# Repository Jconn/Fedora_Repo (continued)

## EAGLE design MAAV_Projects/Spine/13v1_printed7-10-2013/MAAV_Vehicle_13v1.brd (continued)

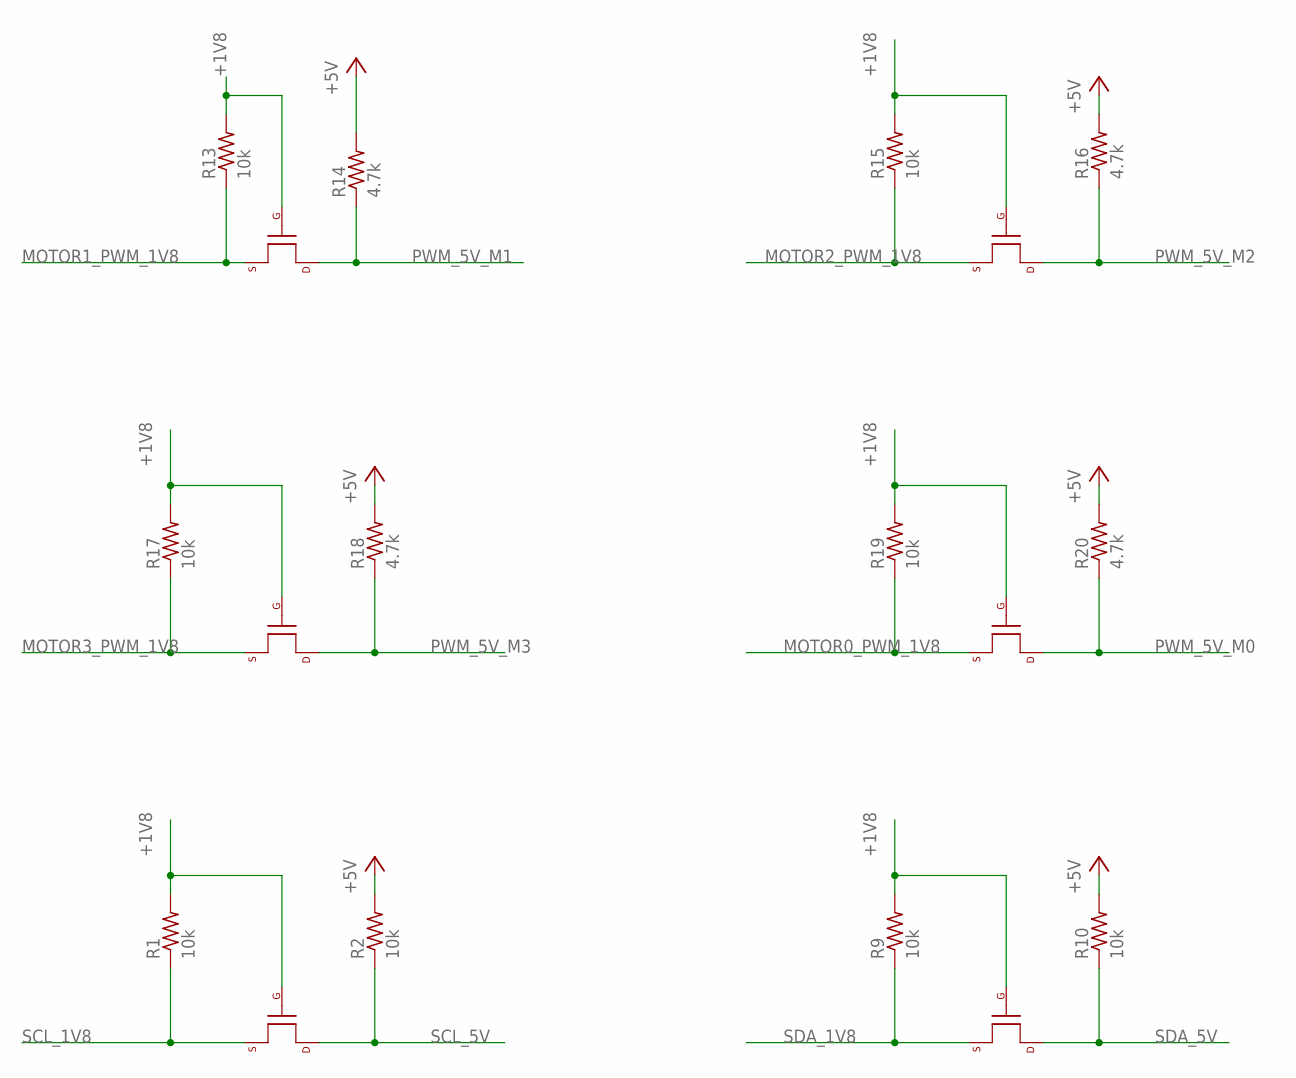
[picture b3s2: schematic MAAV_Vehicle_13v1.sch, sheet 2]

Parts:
R1, R2, R9, R10, R13, R15, R17, R19: 10k; R0603; DIGIKEY# P10.0KHCT-ND
R14, R16, R18, R20: 4.7k; R0603; DIGIKEY# P4.70KHCT-ND
T3, T4, T7, T8, T9, T10: MOSFET-NCHANNELSMD; SOT23-3; DIGIKEY# BSS138KCT-ND

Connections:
+1V8: R1.2, R9.2, R13.2, R15.2, R17.2, R19.2, T3.1 (G), T4.1 (G), T7.1 (G), T8.1 (G), T9.1 (G), T10.1 (G); also elsewhere on the board
+5V: R2.2, R10.2, R14.2, R16.2, R18.2, R20.2; also elsewhere on the board
MOTOR0_PWM_1V8: R19.1, T10.2 (S); also elsewhere on the board
MOTOR1_PWM_1V8: R13.1, T7.2 (S); also elsewhere on the board
MOTOR2_PWM_1V8: R15.1, T8.2 (S); also elsewhere on the board
MOTOR3_PWM_1V8: R17.1, T9.2 (S); also elsewhere on the board
PWM_5V_M0: R20.1, T10.3 (D); also elsewhere on the board
PWM_5V_M1: R14.1, T7.3 (D); also elsewhere on the board
PWM_5V_M2: R16.1, T8.3 (D); also elsewhere on the board
PWM_5V_M3: R18.1, T9.3 (D); also elsewhere on the board
SCL_1V8: R1.1, T3.2 (S); also elsewhere on the board
SCL_5V: R2.1, T3.3 (D); also elsewhere on the board
SDA_1V8: R9.1, T4.2 (S); also elsewhere on the board
SDA_5V: R10.1, T4.3 (D); also elsewhere on the board

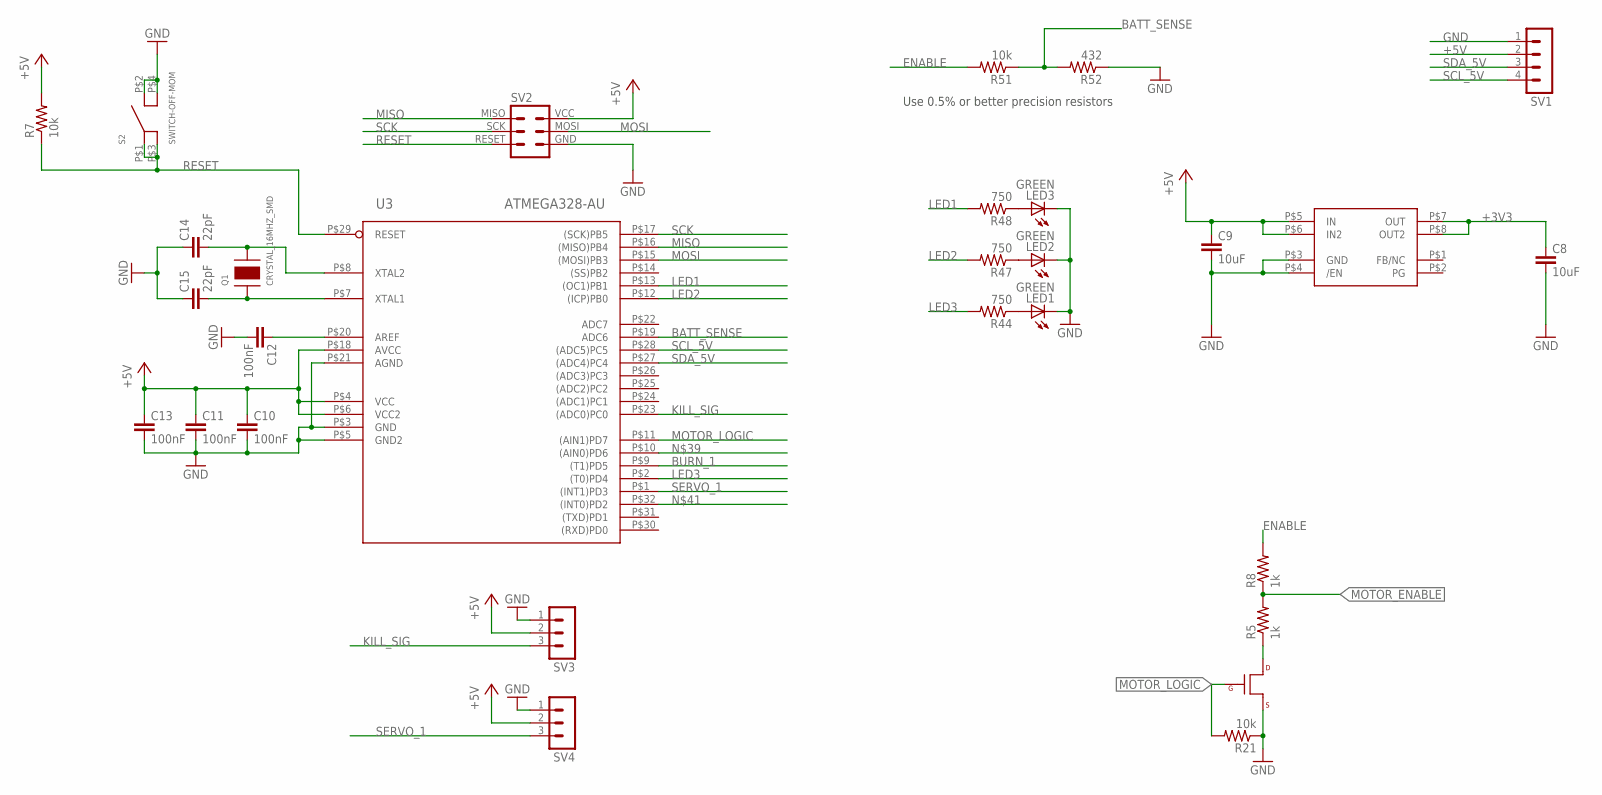
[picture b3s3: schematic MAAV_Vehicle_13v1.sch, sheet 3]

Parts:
C8, C9: 10uF; C1206; DIGIKEY# 587-2399-1-ND
C10, C11, C12, C13: 100nF; C0603; DIGIKEY# 1276-1000-1-ND
C14, C15: 22pF; C0603; DIGIKEY# 478-6200-1-ND
LED1, LED2, LED3: GREEN; CHIPLED_0603; DIGIKEY# 1080-1405-1-ND
Q1: CRYSTAL_16MHZ_SMD; 4-SMD_DFN
R5, R8: 1k; R0603; DIGIKEY# P1.00KHCT-ND
R7, R21: 10k; R0603; DIGIKEY# P10.0KHCT-ND
R44, R47, R48: 750; R0805; DIGIKEY# P750CCT-ND
R51: 10k; R0603; DIGIKEY# P10KDBCT-ND
R52: 432; R0603; DIGIKEY# P432DBCT-ND
S2: SWITCH-OFF-MOM; DIGIKEY# P11084SCT-ND
SV1: MA04-1
SV2: AVRISP-63X2_SMD; AVRISP-6-SMD
SV3, SV4: MA03-1; DIGIKEY# 3M9477-ND
T11: MOSFET-NCHANNELSMD; SOT23-3; DIGIKEY# BSS138KCT-ND
U3: ATMEGA328-AU; 32-TQFP; DIGIKEY# ATMEGA328-AU-ND
U4: REG_3V_8SOIC; 8-SOIC; DIGIKEY# 296-2719-5-ND

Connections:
+3V3: C8.1, U4.P$7 (OUT), U4.P$8 (OUT2)
+5V: C9.1, C10.1, C11.1, C13.1, R7.2, SV1.2, SV2.VCC, SV3.2, SV4.2, U3.P$4 (VCC), U3.P$6 (VCC2), U3.P$18 (AVCC), U4.P$5 (IN), U4.P$6 (IN2); also elsewhere on the board
BATT_SENSE: R51.1, R52.2, U3.P$19 (ADC6)
BURN_1: U3.P$9 ((T1)PD5); also elsewhere on the board
ENABLE: R8.2, R51.2; also elsewhere on the board
GND: C8.2, C9.2, C10.2, C11.2, C12.2, C13.2, C14.1, C15.1, LED1.C, LED2.C, LED3.C, R21.1, R52.1, S2.P$2 (P2), S2.P$4 (P4), SV1.1, SV2.GND, SV3.1, SV4.1, T11.2 (S), U3.P$3 (GND), U3.P$5 (GND2), U3.P$21 (AGND), U4.P$3 (GND), U4.P$4 (/EN); also elsewhere on the board
KILL_SIG: SV3.3, U3.P$23 ((ADC0)PC0)
LED1: R48.2, U3.P$13 ((OC1)PB1)
LED2: R47.2, U3.P$12 ((ICP)PB0)
LED3: R44.2, U3.P$2 ((T0)PD4)
MISO: SV2.MISO, U3.P$16 ((MISO)PB4)
MOSI: SV2.MOSI, U3.P$15 ((MOSI)PB3)
MOTOR_ENABLE: R5.2, R8.1; also elsewhere on the board
MOTOR_LOGIC: R21.2, T11.1 (G), U3.P$11 ((AIN1)PD7)
unnamed: LED1.A, R44.1
unnamed: C12.1, U3.P$20 (AREF)
unnamed: C14.2, Q1.X2, U3.P$8 (XTAL2)
unnamed: R5.1, T11.3 (D)
unnamed: C15.2, Q1.X1, U3.P$7 (XTAL1)
unnamed: LED2.A, R47.1
unnamed: LED3.A, R48.1
RESET: R7.1, S2.P$1 (P1), S2.P$3 (P3), SV2.RESET, U3.P$29 (RESET)
SCK: SV2.SCK, U3.P$17 ((SCK)PB5)
SCL_5V: SV1.4, U3.P$28 ((ADC5)PC5); also elsewhere on the board
SDA_5V: SV1.3, U3.P$27 ((ADC4)PC4); also elsewhere on the board
SERVO_1: SV4.3, U3.P$1 ((INT1)PD3)

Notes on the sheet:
Use 0.5% or better precision resistors

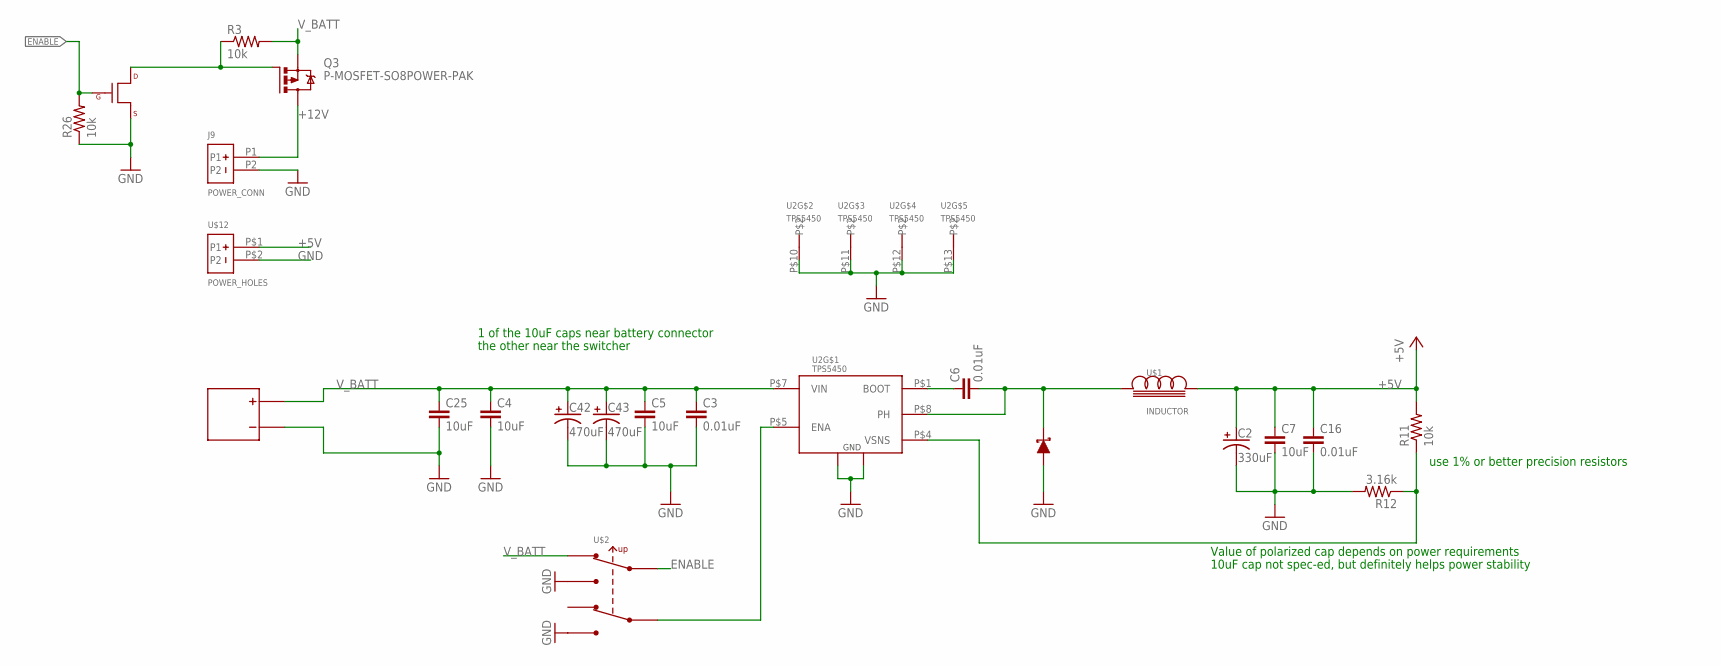
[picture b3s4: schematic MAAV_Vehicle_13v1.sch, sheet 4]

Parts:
C2: 330uF; C_2917_POL; DIGIKEY# 478-1811-1-ND
C3, C6, C16: 0.01uF; C0603; DIGIKEY# 490-1512-1-ND
C4, C5, C7, C25: 10uF; C1206; DIGIKEY# 587-2399-1-ND
C42, C43: 470uF; EH22-9; DIGIEKY# P14440-ND
J9: POWER_CONN
Q2: MOSFET-NCHANNELSMD; SOT23-3; DIGIKEY# BSS84CT-ND
Q3: P-MOSFET-SO8POWER-PAK; SO-8_POWER-PAK; DIGIKEY# SI7135DP-T1-GE3CT-ND
R3, R26: 10k; R0603; DIGIKEY# P10.0KHCT-ND
R11: 10k; R0603; DIGIKEY# P10KDBCT-ND
R12: 3.16k; R0603; DIGIKEY# 311-3.16KDCT-ND
U2: TPS5450; DIGIKEY# 296-23750-1-ND
U$1: INDUCTOR; CDRH127; DIGIEKY# 308-1333-1-ND
U$2: SWITCH_DPDT; SWITCH_VERT_DPDT
U$9: DIODE-SCHOTTKYBIG; DO-214AB,SMC
U$12: POWER_HOLES
U$13: BATTERY50A; LIPO_POWER_50A

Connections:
+5V: C2.A (ANODE), C7.1, C16.1, R11.2, U$1.P2 (2), U$12.P$1 (P1); also elsewhere on the board
+12V: J9.P1, Q3.D1, Q3.D2 (D1), Q3.D3 (D1), Q3.D4 (D1), Q3.D5 (D1); also elsewhere on the board
ENABLE: Q2.1 (G), R26.2, U$2.P$5; also elsewhere on the board
GND: C2.C (CATHODE), C3.2, C4.2, C5.2, C7.2, C16.2, C25.2, C42.G (CATHODE), C43.G (CATHODE), J9.P2, Q2.2 (S), R12.2, R26.1, U2.P$6 (GND), U2.P$9 (PGND), U2.P$10, U2.P$11, U2.P$12, U2.P$13, U$2.P$1, U$2.P$4, U$9.A, U$12.P$2 (P2), U$13.GND; also elsewhere on the board
unnamed: R11.1, R12.1, U2.P$4 (VSNS)
unnamed: C6.1, U2.P$1 (BOOT)
unnamed: U2.P$5 (ENA), U$2.P$2
unnamed: Q2.3 (D), Q3.G, R3.1
unnamed: C6.2, U2.P$8 (PH), U$1.P1 (1), U$9.C
V_BATT: C3.1, C4.1, C5.1, C25.1, C42.P (ANODE), C43.P (ANODE), Q3.S1, Q3.S2 (S1), Q3.S3 (S1), R3.2, U2.P$7 (VIN), U$2.P$6, U$13.BATT; also elsewhere on the board

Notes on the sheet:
Value of polarized cap depends on power requirements
10uF cap not spec-ed, but definitely helps power stability
1 of the 10uF caps near battery connector
the other near the switcher
use 1% or better precision resistors

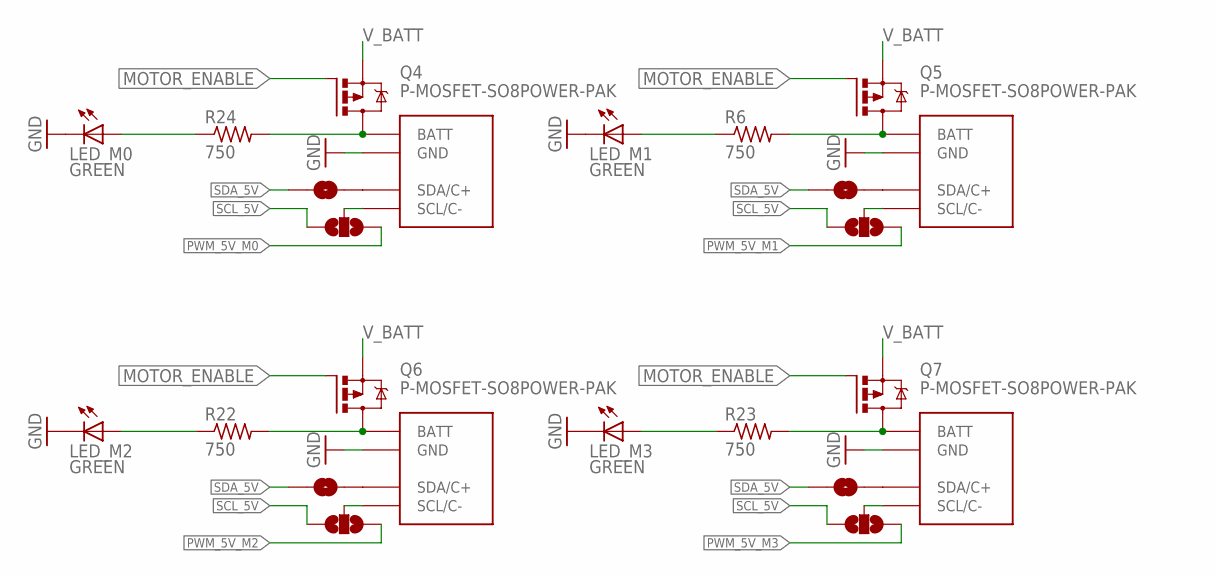
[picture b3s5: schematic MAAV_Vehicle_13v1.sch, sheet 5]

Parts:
LED_M0, LED_M1, LED_M2, LED_M3: GREEN; CHIPLED_0805
Q4, Q5, Q6, Q7: P-MOSFET-SO8POWER-PAK; SO-8_POWER-PAK
R6, R22, R23, R24: 750; R0805; DIGIKEY# P750CCT-ND
SJ1, SJ2, SJ5, SJ7: SOLDERJUMPERNO; SJ_2S-NO
SJ3, SJ4, SJ6, SJ8: SOLDERJUMPER_2WAYS; SJ_3
U$3, U$4, U$5, U$6: ESC_CONN

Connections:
GND: LED_M0.C, LED_M1.C, LED_M2.C, LED_M3.C, U$3.GND, U$4.GND, U$5.GND, U$6.GND; also elsewhere on the board
MOTOR_ENABLE: Q4.G, Q5.G, Q6.G, Q7.G; also elsewhere on the board
unnamed: Q4.D1, Q4.D2 (D1), Q4.D3 (D1), Q4.D4 (D1), Q4.D5 (D1), R24.2, U$3.BATT
unnamed: SJ2.2, U$3.SDA/C+
unnamed: SJ3.2, U$3.SCL/C-
unnamed: LED_M0.A, R24.1
unnamed: Q5.D1, Q5.D2 (D1), Q5.D3 (D1), Q5.D4 (D1), Q5.D5 (D1), R6.2, U$4.BATT
unnamed: LED_M1.A, R6.1
unnamed: SJ1.2, U$4.SDA/C+
unnamed: SJ4.2, U$4.SCL/C-
unnamed: Q6.D1, Q6.D2 (D1), Q6.D3 (D1), Q6.D4 (D1), Q6.D5 (D1), R22.2, U$5.BATT
unnamed: LED_M2.A, R22.1
unnamed: SJ5.2, U$5.SDA/C+
unnamed: SJ6.2, U$5.SCL/C-
unnamed: Q7.D1, Q7.D2 (D1), Q7.D3 (D1), Q7.D4 (D1), Q7.D5 (D1), R23.2, U$6.BATT
unnamed: LED_M3.A, R23.1
unnamed: SJ7.2, U$6.SDA/C+
unnamed: SJ8.2, U$6.SCL/C-
PWM_5V_M0: SJ3.1; also elsewhere on the board
PWM_5V_M1: SJ4.1; also elsewhere on the board
PWM_5V_M2: SJ6.1; also elsewhere on the board
PWM_5V_M3: SJ8.1; also elsewhere on the board
SCL_5V: SJ3.3, SJ4.3, SJ6.3, SJ8.3; also elsewhere on the board
SDA_5V: SJ1.1, SJ2.1, SJ5.1, SJ7.1; also elsewhere on the board
V_BATT: Q4.S1, Q4.S2 (S1), Q4.S3 (S1), Q5.S1, Q5.S2 (S1), Q5.S3 (S1), Q6.S1, Q6.S2 (S1), Q6.S3 (S1), Q7.S1, Q7.S2 (S1), Q7.S3 (S1); also elsewhere on the board

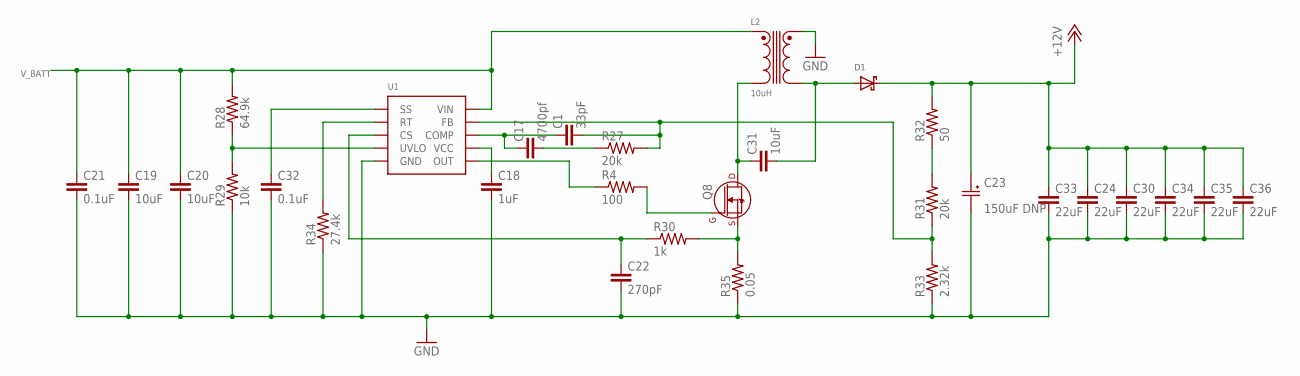
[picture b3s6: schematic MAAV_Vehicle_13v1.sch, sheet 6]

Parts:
C1: 33pF; C0402; DIGIKEY# box
C17: 4700pf; C0402; DIGIKEY# box
C18: 1uF; C0603; DIGIKEY# 587-2984-1-ND
C19, C20, C31: 10uF; C1206; DIGIKEY# 587-2399-1-ND
C21: 0.1uF; C0603; DIGIKEY# 1276-1000-1-ND
C22: 270pF; C0402; DIGIKEY# box
C23: 150uF DNP; C2917
C24, C30, C33, C34, C35, C36: 22uF; C1206; DIGIKEY# 587-3246-1-ND
C32: 0.1uF; C0402; DIGIKEY# box
D1: PDS760; DIGIKEY# PDS760DICT-ND
L2: 10uH; DRQ125
Q8: STL60N3LLH5; POWERFLAT-8
R4: 100; R0402; DIGIKEY# box
R27, R31: 20k; R0402; DIGIKEY# box
R28: 64.9k; R0402; DIGIKEY# P64.9KDCCT-ND
R29: 10k; R0402; DIGIKEY# box
R30: 1k; R0402; DIGIKEY# box
R32: 50; R0402; DIGIKEY# box
R33: 2.32k; R0402; DIGIKEY# P2.32KDCCT-ND
R34: 27.4k; R0402; DIGIKEY# box
R35: 0.05; R2512; DIGIKEY# MCS3264R050FERCT-ND
U1: LM5022; MSOP-10

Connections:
+12V: C23.+, C24.1, C30.1, C33.1, C34.1, C35.1, C36.1, D1.C (CATHODE), R32.2; also elsewhere on the board
COMP: C1.1, C17.1, U1.P$3 (COMP)
CS: C22.1, R30.1, U1.P$8 (CS)
FB2: C1.2, R27.2, R31.1, R33.2, U1.P$2 (FB)
GND: C18.2, C19.2, C20.2, C21.2, C22.2, C23.-, C24.2, C30.2, C32.2, C33.2, C34.2, C35.2, C36.2, L2.2, R29.1, R33.1, R34.1, R35.1, U1.P$6 (GND); also elsewhere on the board
unnamed: C17.2, R27.1
unnamed: Q8.P$4 (G), R4.2
unnamed: C31.2, D1.A1 (ANODE), D1.A2 (ANODE), L2.4
unnamed: R31.2, R32.1
OUT: R4.1, U1.P$5 (OUT)
Q3_D: C31.1, L2.3, Q8.P$5 (D)
Q3_S: Q8.P$1 (S), Q8.P$2 (S), Q8.P$3 (S), R30.2, R35.2
RT: R34.2, U1.P$9 (RT)
SS2: C32.1, U1.P$10 (SS)
UVLO: R28.1, R29.2, U1.P$7 (UVLO)
VCC2: C18.1, U1.P$4 (VCC)
V_BATT: C19.1, C20.1, C21.1, L2.1, R28.2, U1.P$1 (VIN); also elsewhere on the board

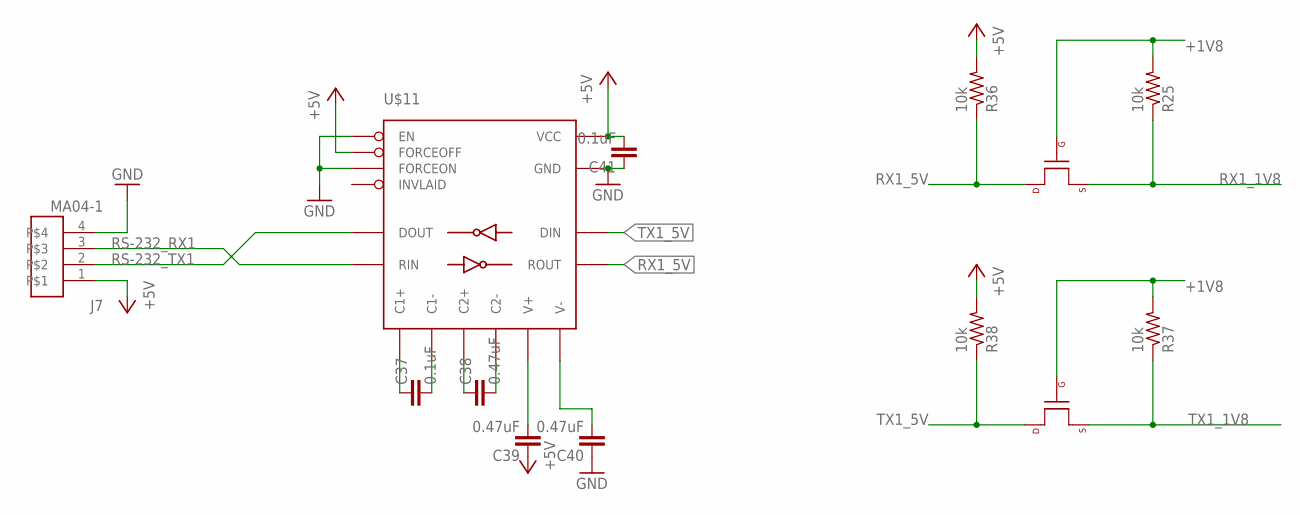
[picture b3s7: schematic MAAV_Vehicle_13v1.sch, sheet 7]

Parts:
C37, C41: 0.1uF; C0603; DIGIKEY# 490-1524-1-ND
C38, C39, C40: 0.47uF; C0805; DIGIKEY# 1276-2966-1-ND
J7: MA04-1; MA-04-SMD
R25, R36, R37, R38: 10k; R0603; DIGIKEY# P10.0KHCT-ND
T1, T2: MOSFET-NCHANNELSMD; SOT23-3; DIGIKEY# BSS138KCT-ND
U$11: MAX3221-RS232; 16-TSSOP; DIGIKEY# 296-19825-1-ND

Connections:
+1V8: R25.2, R37.2, T1.1 (G), T2.1 (G); also elsewhere on the board
+5V: C39.1, C41.2, J7.1, R36.2, R38.2, U$11.P$15 (VCC), U$11.P$16 (FORCEOFF); also elsewhere on the board
GND: C40.1, C41.1, J7.4, U$11.P$1 (EN), U$11.P$12 (FORCEON), U$11.P$14 (GND); also elsewhere on the board
unnamed: C37.1, U$11.P$2 (C1+)
unnamed: C37.2, U$11.P$4 (C1-)
unnamed: C38.1, U$11.P$5 (C2+)
unnamed: C38.2, U$11.P$6 (C2-)
unnamed: C39.2, U$11.P$3 (V+)
unnamed: C40.2, U$11.P$7 (V-)
RS-232_RX1: J7.3, U$11.P$8 (RIN)
RS-232_TX1: J7.2, U$11.P$13 (DOUT)
RX1_1V8: R25.1, T1.2 (S); also elsewhere on the board
RX1_5V: R36.1, T1.3 (D), U$11.P$9 (ROUT)
TX1_1V8: R37.1, T2.2 (S); also elsewhere on the board
TX1_5V: R38.1, T2.3 (D), U$11.P$11 (DIN)

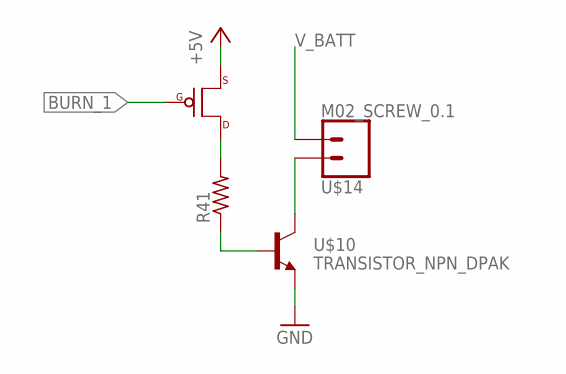
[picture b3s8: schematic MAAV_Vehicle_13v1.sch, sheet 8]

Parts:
R41: R-USR1206; R1206; DIGIKEY# P100FCT-ND, P68.1FCT-ND, P200FCT-ND
U$10: TRANSISTOR_NPN_DPAK; DPAK; DIGIKEY# 497-12849-1-ND
U$14: M02_SCREW_0.1; SCREW_TERM_2POS
U$15: MOSFET-PCHANNEL_SOT23-3; SOT23-3; DIGIKEY# BSS84CT-ND

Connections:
+5V: U$15.3 (D); also elsewhere on the board
BURN_1: U$15.1 (G); also elsewhere on the board
GND: U$10.3 (E); also elsewhere on the board
unnamed: U$10.TAB (C), U$14.P$2 (4)
unnamed: R41.2, U$15.2 (S)
unnamed: R41.1, U$10.1 (B)
V_BATT: U$14.P$1 (3); also elsewhere on the board

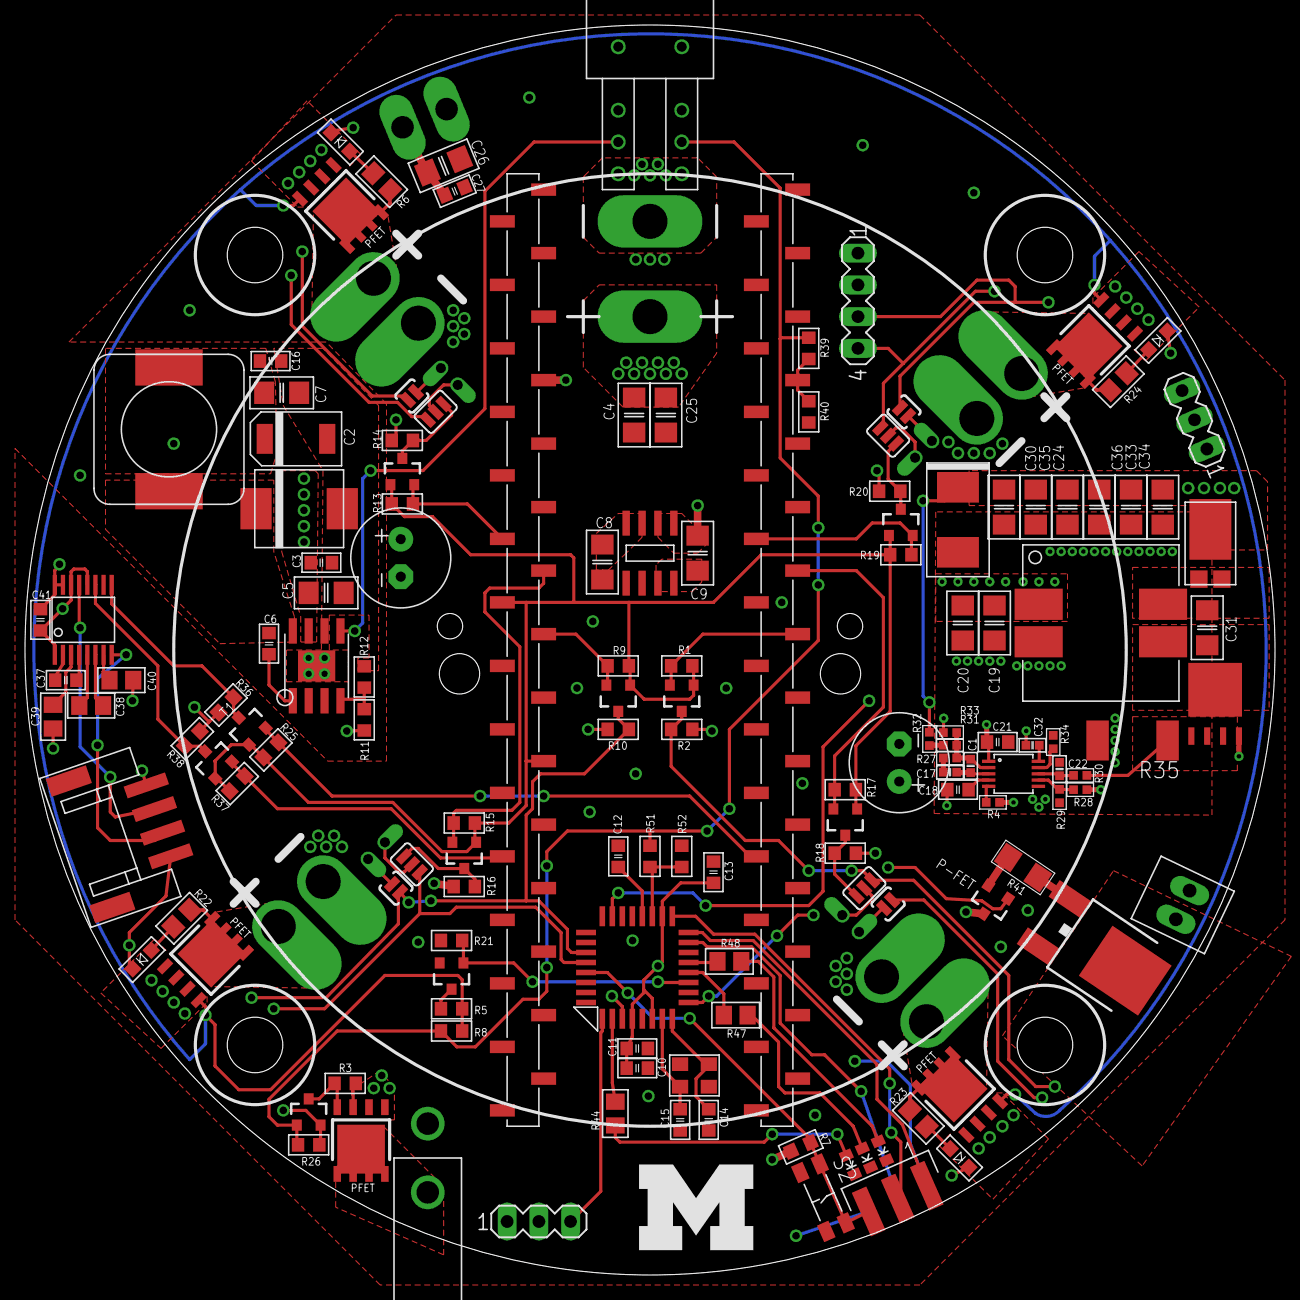
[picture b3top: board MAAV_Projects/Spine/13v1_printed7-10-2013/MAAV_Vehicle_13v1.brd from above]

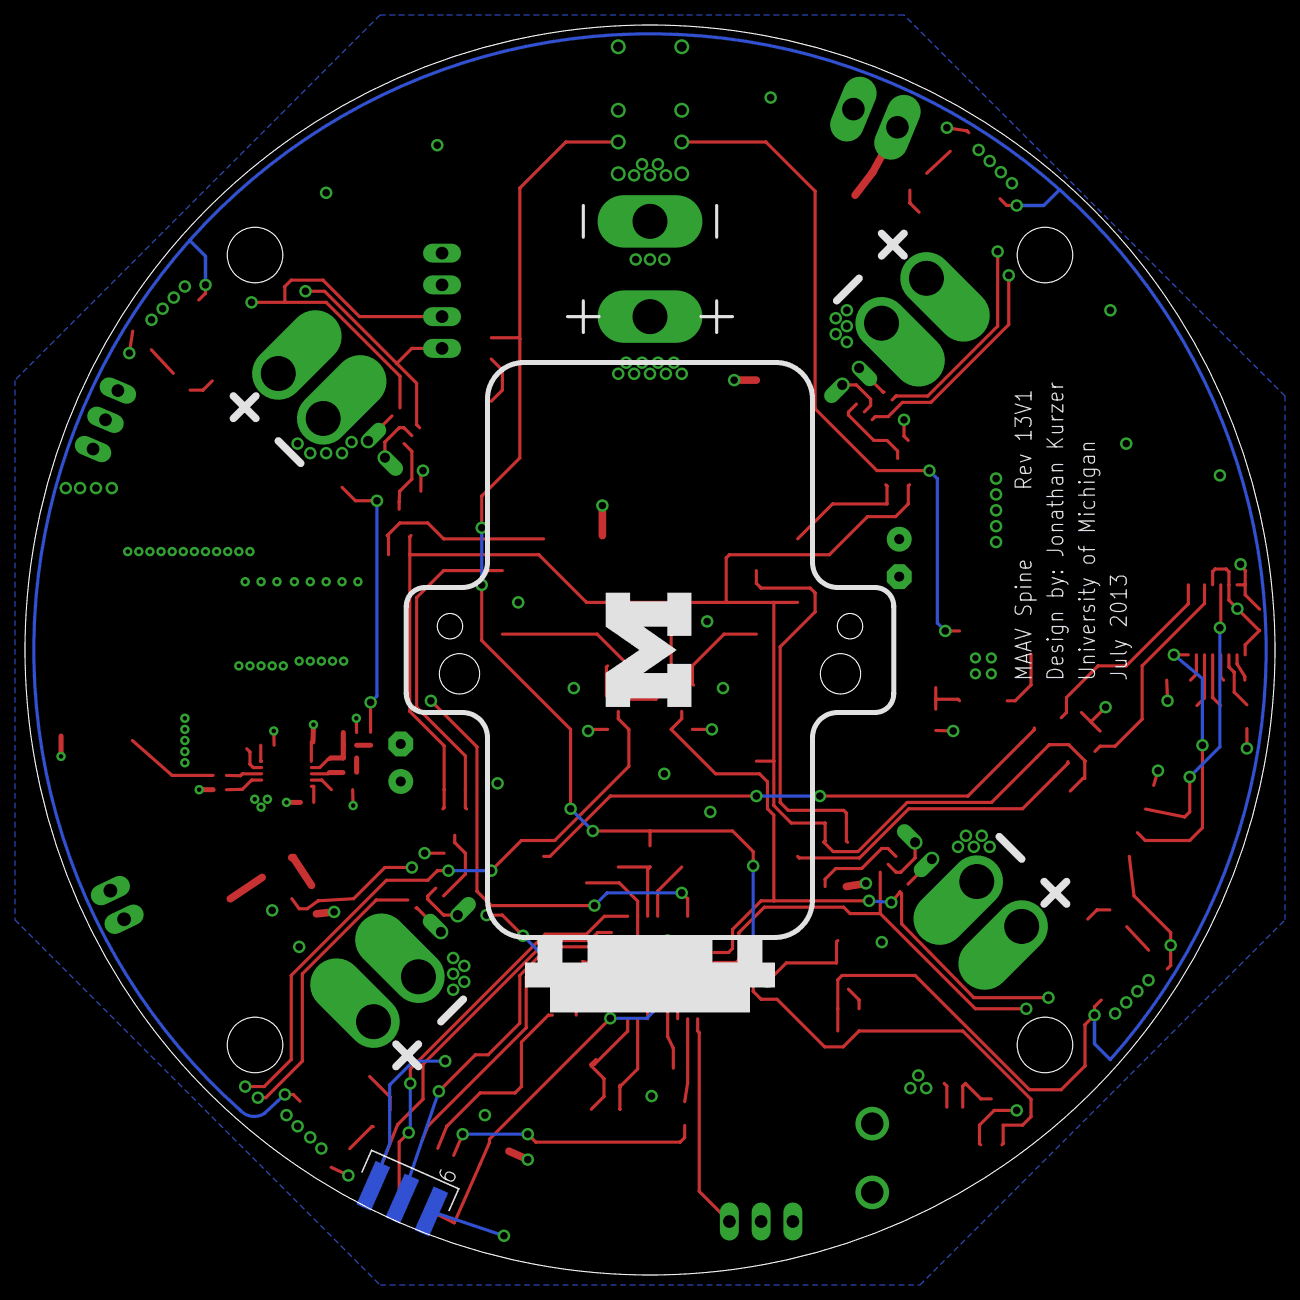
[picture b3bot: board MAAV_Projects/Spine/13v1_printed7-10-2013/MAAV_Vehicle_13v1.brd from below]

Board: 4 copper layers, 100.0 x 100.0 mm, 149 parts (3 on the bottom side), 90 nets.

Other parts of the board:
U$7, U$16: BLOCK-M-10MMW
U$8: IMU

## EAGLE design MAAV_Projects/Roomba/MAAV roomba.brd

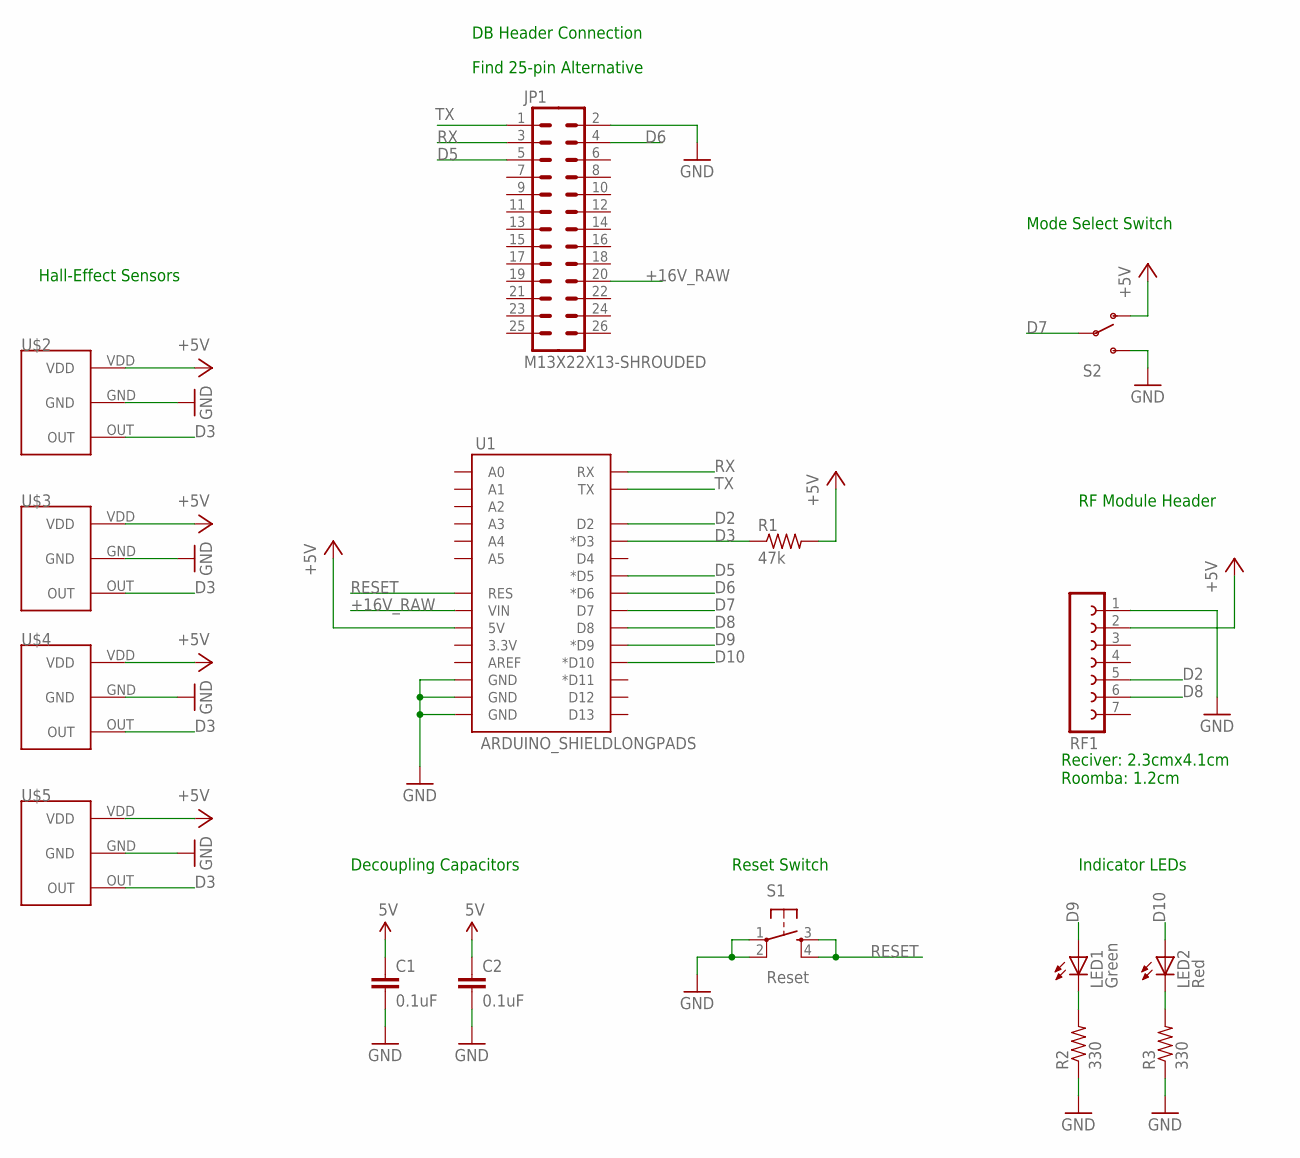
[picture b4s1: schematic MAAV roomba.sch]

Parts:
C1, C2: 0.1uF; CAP-PTH-SMALL2; DIGIKEY 399-4264-ND
JP1: M13X22X13-SHROUDED; 2X25-SHROUDED
LED1: Green; LED5MM; DIGIKEY 1125-1184-ND
LED2: Red; LED5MM; DIGIKEY 1125-1188-ND
R1: 47k; 0309/10; DIGIKEY CF12JT47K0
R2, R3: 330; AXIAL-0.4; DIGIKEY 330QBK-ND
RF1: FE07W; DIGIKEY S5443-ND
S1: Reset; TACTILE-PTH; DIGIKEY 450-1650-ND
S2: SWITCH-SPDTPTH; SWITCH-SPDT; DIGIKEY EG1903-ND
U1: ARDUINO_SHIELDLONGPADS; DUEMILANOVE_SHIELD_LONGPADS
U$2, U$3, U$4, U$5: HALL_EFFECT; MOUSER 621-AH180-PL-A

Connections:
5V: C1.1, C2.1, R1.2, RF1.2, S2.1 (O), U1.5V, U$2.VDD, U$3.VDD, U$4.VDD, U$5.VDD
+16V_RAW: JP1.20, U1.VIN
D2: RF1.5, U1.D2
D3: R1.1, U1.D3 (*D3), U$2.OUT, U$3.OUT, U$4.OUT, U$5.OUT
D5: JP1.5, U1.D5 (*D5)
D6: JP1.4, U1.D6 (*D6)
D7: S2.2, U1.D7
D8: RF1.6, U1.D8
D9: LED1.A, U1.D9 (*D9)
D10: LED2.A, U1.D10 (*D10)
GND: C1.2, C2.2, JP1.2, R2.P$1 (1), R3.P$1 (1), RF1.1, S1.1, S1.2, S2.3 (S), U1.GND@0 (GND), U1.GND@1 (GND), U1.GND@2 (GND), U$2.GND, U$3.GND, U$4.GND, U$5.GND
unnamed: LED1.K (C), R2.P$2 (2)
unnamed: LED2.K (C), R3.P$2 (2)
RESET: S1.3, S1.4, U1.RES
RX: JP1.3, U1.RX
TX: JP1.1, U1.TX

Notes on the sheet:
Hall-Effect Sensors
DB Header Connection
Find 25-pin Alternative
Decoupling Capacitors
Indicator LEDs
Reset Switch
Mode Select Switch
RF Module Header
Reciver: 2.3cmx4.1cm Roomba: 1.2cm

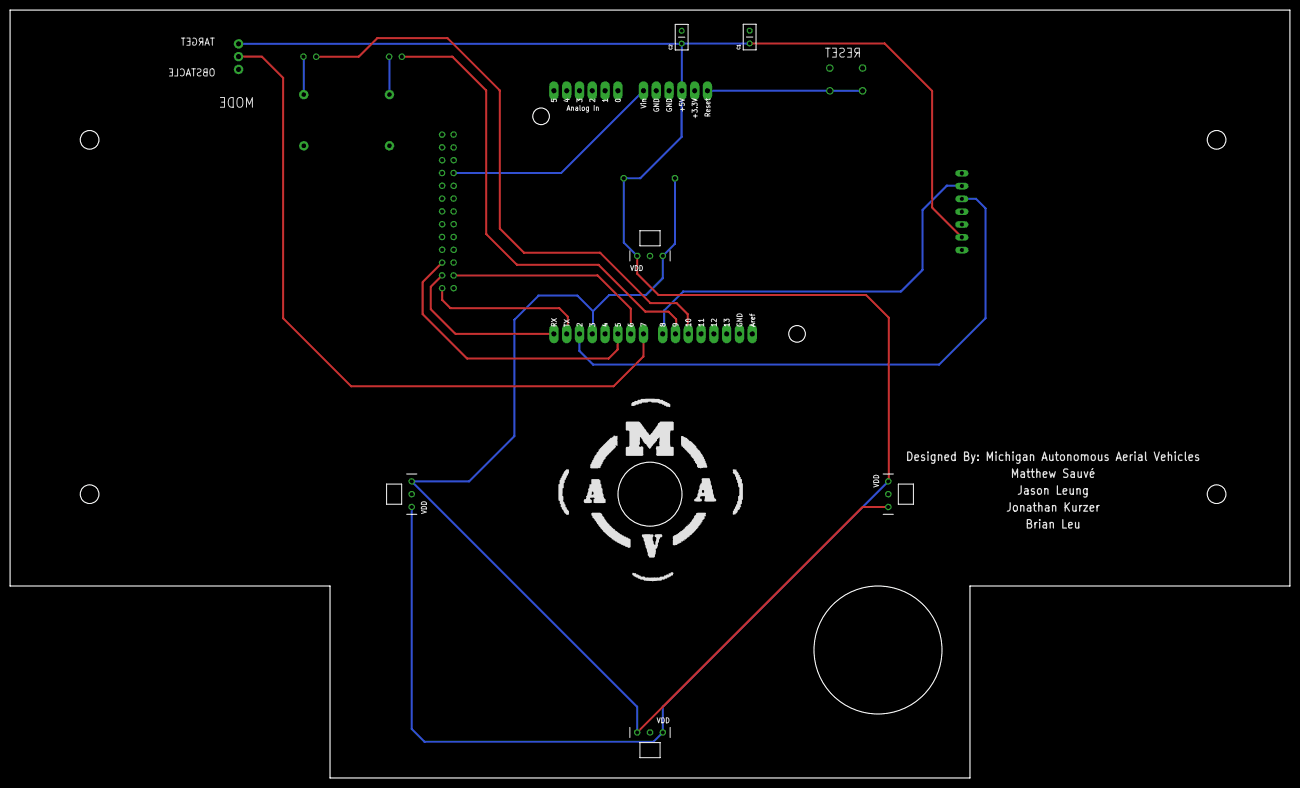
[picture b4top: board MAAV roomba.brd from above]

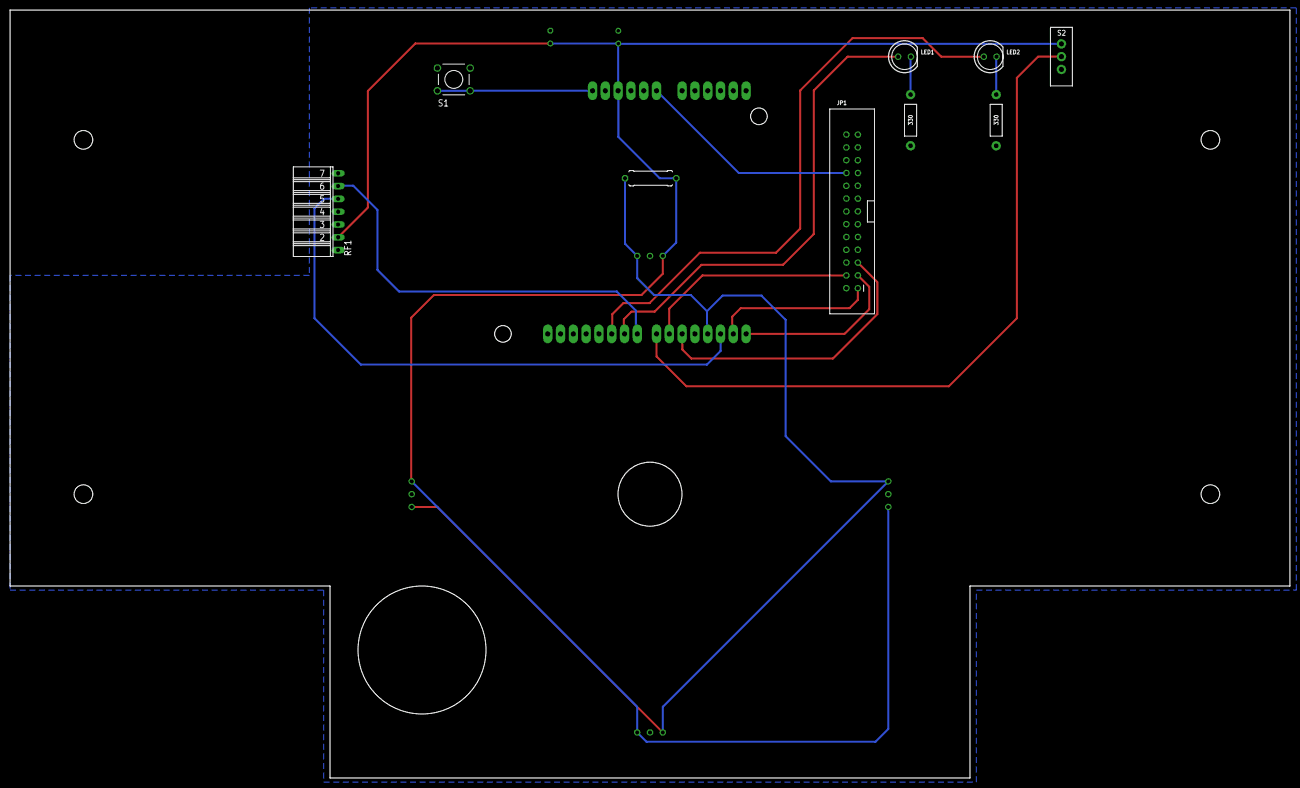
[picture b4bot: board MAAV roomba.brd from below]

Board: 2 copper layers, 254.0 x 152.4 mm, 18 parts (9 on the bottom side), 16 nets.

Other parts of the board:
U$1: IARC_GROUND_OUTLINE
U$6: MAAV_CIRCLE

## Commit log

2014-05-10 renamed some folders
2014-05-10 added lots of files to inital commit
2014-05-12 added MAAV_13v1.lib
2014-05-14 added block-M holes layout to BlockM.lbr
2014-05-14 50mm logo and reformatted README
2014-05-14 modified .gitignore
2014-05-14 addes shild version of romba borard and library to match
2014-05-15 added 2014 version of spine on repo
2014-05-16 added the tag-Connect pakage
2014-05-16 power management systems for Spine14v0
2014-05-18 not sure what's different
2014-05-19 added ULP files folder for open-source ulp files that aren't native to eagle
2014-05-20 added tag connect programming pads
2014-05-20 added avrisp programing header
2014-05-20 changed TC2050-IDC-NL to JTAG_IDC-10. connected all IDC connector layouts to respective 6-pin and 10-pin devices
2014-05-20 fixed pad layout names for 6-pin plug_of_nails connector. should be in correct orientation
2014-05-20 added JTAG programmer for tiva and nets for ATMega
2014-05-20 edited the plug of nails for JTAG connections
2014-05-21 most connections for gunstix, atmega, tiva, and power management systems. need to connect MCU's together and create motor output. consider phoenix edge lite
2014-05-21 fixed 50A power connector (molex?) and added tiva c series to library
2014-05-22 adding px4 connector header
2014-05-22 worked on schematic.. shifted sheets around for 13v1
2014-05-22 added last semester's work on separate modules as reference
2014-05-22 organized components and implemented i2c bus. next is motors
2014-05-22 fixing a small component error
2014-05-22 blah
2014-05-22 too tired. will finish motors later
2014-05-23 most level shifters, and most of motor output. only main things left are SD card and IMU
2014-05-23 pushing again
2014-05-23 changed motor output to 3v3 logic. going to add switches, SD card, and IMU, then i should be finished with schematic
2014-05-23 added Ti-power module to MAAV.lbr
2014-05-23 small modificaions to the MAAV.lbr, I think added atributes
2014-05-24 just need to add switches and IMU and should be done with all the essentials... time to move on to the KNIGHT RIDERRRR. also working on a 4PDT switch
2014-05-24 got rid of 4PDT device. kept symbol
2014-05-29 moved some files around and added SMD version of roomba shiled
2014-06-08 modidified roomba shield
2014-07-08 added the two roomba varients
2014-07-09 started work on Spine 14v1. for the DJI (no gumstix)
2014-07-09 updated dims and holes. added roundovers to hard corners of baord. added a drawing of the body that the board mounts to.
2014-07-11 started routing
2014-07-13 Routed most of the ATMega. Can there be traces in the Route2 layer?
2014-07-13 removed a few traces cuz i didn't realize Top layer was a huge GND polygon. although i fail to see the difference between the Top GND polygon and the Route2 GND polygon
2014-07-14 routed some more (almost finished). Added some micro swtiches to Jon_LIB
2014-07-14 finished JTAG routing. still need to finish the toggle switches
2014-07-14 put in toggle switches and finished routing the baord. Added logo and credits
2014-07-16 Spine 14v1 boards sent to print house
2014-08-20 end of summer push
